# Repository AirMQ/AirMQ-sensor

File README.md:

# AirMQ-sensor
Root repository for AirMQ hardware project

AirMQ toolkit consists of main MCU and several sensor boards designed with common form factor in mind. Currently, particulate matter, radiation and electrochemical sensor boards are available. 

MCU board includes advanced power circuitry which makes possible the use of reduced consumption modes while powering from batteries or solar panels. All ESP8266’s gpio pins are accessible with a separate 16-pin connector sharing pin numbering with most popular development boards. 

All boards share the same type of extension connector which allows for stackability limited by sensors size.

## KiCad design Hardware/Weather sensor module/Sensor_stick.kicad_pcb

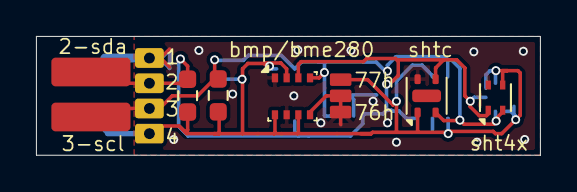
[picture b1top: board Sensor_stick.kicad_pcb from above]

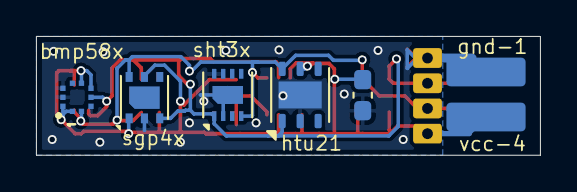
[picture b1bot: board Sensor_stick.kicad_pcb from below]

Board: 2 copper layers, 28.0 x 6.6 mm, 11 parts (5 on the bottom side), 4 nets.

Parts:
C1: 1 uF; C_0603_1608Metric_Pad1.08x0.95mm_HandSolder
J1: Conn_01x04; 4Pads
R1, R2: 4.7K; R_0603_1608Metric_Pad0.98x0.95mm_HandSolder
U1: SHT30-DIS; Sensirion_DFN-8-1EP_2.5x2.5mm_P0.5mm_EP1.1x1.7mm
U2: Si7021-A20; DFN-6-1EP_3x3mm_P1mm_EP1.5x2.4mm
U3: SHT4x; Sensirion_DFN-4_1.5x1.5mm_P0.8mm_SHT4x_NoCentralPad
U4: SHTC3; Sensirion_DFN-4-1EP_2x2mm_P1mm_EP0.7x1.6mm
U5: BME280; Bosch_LGA-8_2.5x2.5mm_P0.65mm_ClockwisePinNumbering
U6: SGP4x
U8: BMP580

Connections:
/SCL: J1.2, R2.2, U1.4 (SCL), U2.6 (SCL), U3.2 (SCL), U4.2 (SCL), U5.4 (SCK), U6.6 (SCL), U8.2 (SCK)
/SDA: J1.1, R1.2, U1.1 (SDA), U2.1 (SDA), U3.1 (SDA), U4.3 (SDA), U5.3 (SDI), U6.3 (SDA), U8.4 (SDI)
/VCC: C1.1, J1.3, R1.1, R2.1, U1.5 (VDD), U1.6 (~RESET), U2.5 (VDD), U3.3 (VDD), U4.1 (VDD), U5.2 (CSB), U5.6 (VDDIO), U5.8 (VDD), U6.1 (VDD), U6.5 (VDDH), U8.1 (VDDIO), U8.5 (SDO), U8.6 (CSB), U8.10 (VDD)
GND: C1.2, J1.4, U1.2 (ADDR), U1.7 (R), U1.8 (VSS), U1.9 (VSS), U2.2 (GND), U2.7 (PAD), U3.4 (VSS), U4.4 (VSS), U5.1 (GND), U5.7 (GND), U6.2 (VSS), U8.3 (VSS), U8.8 (VSS), U8.9 (VSS)

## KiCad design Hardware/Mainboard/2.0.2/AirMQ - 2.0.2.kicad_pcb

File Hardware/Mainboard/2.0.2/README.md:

# Mainboard version 2.0.2

Changelog:

3D view

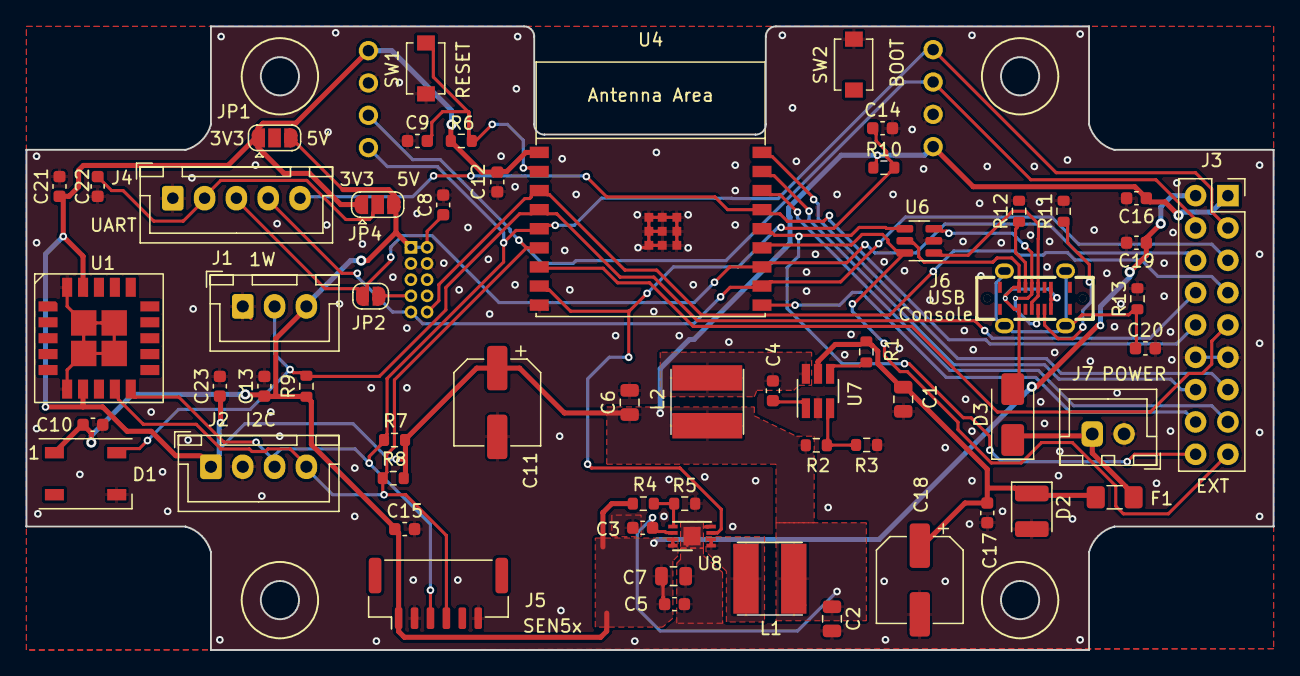
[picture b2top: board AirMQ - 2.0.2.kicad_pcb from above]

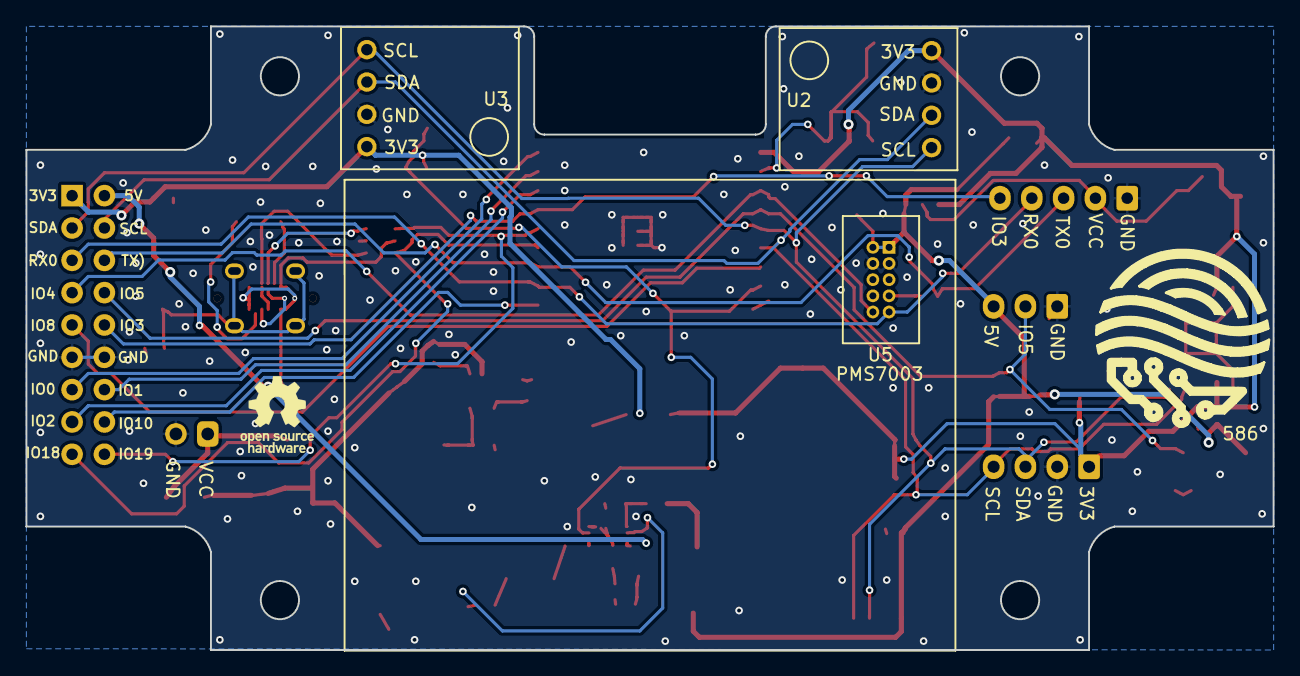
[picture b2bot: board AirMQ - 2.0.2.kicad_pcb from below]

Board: 2 copper layers, 98.0 x 49.0 mm, 63 parts (4 on the bottom side), 35 nets.

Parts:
586: AirMQ_Logo; AirMQ_Logo_new
C1, C2: 10 uF; C_0805_2012Metric
C3, C5, C10, C12, C13, C14, C15, C17, C20, C21, C22, C23: 0.1 uF; C_0603_1608Metric
C4: 22 nF; C_0603_1608Metric
C6, C7: 22 uF; C_0805_2012Metric
C8: 0.1; C_0603_1608Metric
C9, C16, C19: 1 uF; C_0603_1608Metric
C11: 330 uF; CP_Elec_6.3x7.7
C18: 100 uF; CP_Elec_6.3x7.7
D1: WS2812B; LED_WS2812B_PLCC4_5.0x5.0mm_P3.2mm
D2: D_TVS; D_1210_3225Metric
D3: SC34; D_SMA
F1: 0.5A; Fuse_1206_3216Metric_Pad1.42x1.75mm_HandSolder
J1: 1Wire/LED; JST_XH_B3B-XH-A_1x03_P2.50mm_Vertical
J2: I2C; JST_XH_B4B-XH-A_1x04_P2.50mm_Vertical
J3: EXT; PinSocket_2x09_P2.54mm_Vertical
J4: UART; JST_XH_B5B-XH-A_1x05_P2.50mm_Vertical
J5: SEN5x; JST_GH_BM06B-GHS-TBT_1x06-1MP_P1.25mm_Vertical
J6: USB_C; USB-C-SMD_TYPEC-303-ACP16
J7: MAIN_PWR; JST_XH_B2B-XH-A_1x02_P2.50mm_Vertical
JP1, JP4: SolderJumper_3_Open; SolderJumper-3_P1.3mm_Open_RoundedPad1.0x1.5mm
JP2: TX; SolderJumper-2_P1.3mm_Open_RoundedPad1.0x1.5mm
L1: 2.2 uH; Inductor_CD53
L2: 4.7 uH; Inductor_CD53
R1: 100k; R_0603_1608Metric
R2: 150k; R_0603_1608Metric
R3: 33k; R_0603_1608Metric
R4: 510k; R_0603_1608Metric
R5: 160k; R_0603_1608Metric
R6, R7, R8, R10: 10k; R_0603_1608Metric
R9: 4.7k; R_0603_1608Metric
R11, R12: 5.1k; R_0603_1608Metric
R13: 0R; R_0603_1608Metric
SW1: RESET; SW_PUSH_4x3x2
SW2: BOOT; SW_PUSH_4x3x2
U1: SCD40
U2, U3: GY-Sensor; GY-BMEP
U4: ESP32-C3-WROOM-02
U5: PMS7003
U6: USBLC6-2SC6; SOT-23-6
U7: STI3470; SOT-23-6_Handsoldering
U8: SY7088; DFN-8-1EP_3x2mm_P0.5mm_EP1.36x1.46mm

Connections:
+3V3: C2.1, C3.1, C6.1, C11.1, C12.1, C16.1, C21.1, C23.1, J2.1, J3.1, JP1.1 (A), JP4.1 (A), L1.1, L2.2, R2.1, R6.1, R7.1, R8.1, R10.1, U1.7 (VDD), U1.19 (VDDH), U2.1 (VCC), U3.1 (VCC), U4.1 (3V3), U8.6 (IN)
+5V: C5.1, C7.1, C8.1, C10.1, C13.1, C15.1, C19.1, D1.1 (VDD), J1.3, J3.2, J5.1, JP1.3 (B), JP4.3 (B), R4.1, R9.1, U5.1 (VCC), U5.2 (VCC), U8.7 (OUT), U8.8 (OUT)
/D+: J3.18, U4.14 (GPIO19/USB_D+), U6.4 (I/O2)
/D-: J3.17, U4.13 (GPIO18/USB_D-), U6.6 (I/O1)
/EN: C9.2, R6.2, SW1.2, U4.2 (EN/CHIP_PU)
/IO0: J3.13, U4.18 (GPIO0)
/IO1: J3.14, U4.17 (GPIO1)
/IO2: J3.15, U4.16 (GPIO2)
/IO3: J3.10, J4.5, U4.15 (GPIO3)
/IO4: J3.7, U4.3 (GPIO4), U5.10 (SET)
/IO5: D1.4 (DIN), J1.2, J3.8, R9.2, U4.4 (GPIO5)
/IO8: J3.9, U4.7 (GPIO8)
/IO9: C14.1, R10.2, U4.8 (GPIO9), U8.3 (EN)
/IO10: J3.16, U4.10 (GPIO10)
/RX0: J3.5, J4.4, U4.11 (GPIO20/U0RXD), U5.9 (TX)
/SCL: J2.4, J3.4, J5.4, R8.2, U1.9 (SCL), U2.3 (SCL), U3.3 (SCL), U4.6 (GPIO7)
/SDA: J2.3, J3.3, J5.3, R7.2, U1.10 (SDA), U2.4 (SDA), U3.4 (SDA), U4.5 (GPIO6)
/TX0: J3.6, J4.3, JP2.1 (A), U4.12 (GPIO21/U0TXD)
GND: C1.2, C2.2, C3.2, C5.2, C6.2, C7.2, C8.2, C9.1, C10.2, C11.2, C12.2, C13.2, C14.2, C15.2, C16.2, C17.2, C18.2, C19.2, C20.2, C21.2, C22.2, C23.2, D1.3 (VSS), D2.2 (A2), J1.1, J2.2, J3.11, J3.12, J4.1, J5.2, J5.6, J7.1, R3.2, R5.2, R11.2, R12.2, R13.2, SW1.1, SW2.2, U1.6 (GND), U1.20 (GND), U1.21 (GND), U2.2 (GND), U3.2 (GND), U4.9 (GND), U4.19 (GND), U5.3 (GND), U5.4 (GND), U6.2 (GND), U7.2 (GND), U8.4 (SGND), U8.9 (PGND)
unnamed: D3.2 (A), J6.A4 (VBUS), J6.A9 (VBUS), J6.B4 (VBUS), J6.B9 (VBUS), U6.5 (VBUS)
unnamed: D3.1 (K), F1.2, J7.2
unnamed: C22.1, J4.2, JP4.2 (C)
unnamed: J6.A5 (CC1), R11.1
unnamed: J6.B5 (CC2), R12.1
unnamed: J6.A6 (D+), J6.B6 (D+), U6.3 (I/O2)
unnamed: J6.A7 (D-), J6.B7 (D-), U6.1 (I/O1)
unnamed: C20.1, J6.S1 (SHIELD), R13.1
unnamed: JP2.2 (B), U5.7 (RX)
unnamed: L1.2, U8.1 (LX), U8.2 (LX)
unnamed: C4.1, U7.1 (BS)
unnamed: R1.2, U7.4 (EN)
unnamed: R2.2, R3.1, U7.3 (FB)
unnamed: C4.2, L2.1, U7.6 (LX)
unnamed: R4.2, R5.1, U8.5 (FB)
VCC: C1.1, C17.1, C18.1, D2.1 (A1), F1.1, R1.1, U7.5 (VIN)

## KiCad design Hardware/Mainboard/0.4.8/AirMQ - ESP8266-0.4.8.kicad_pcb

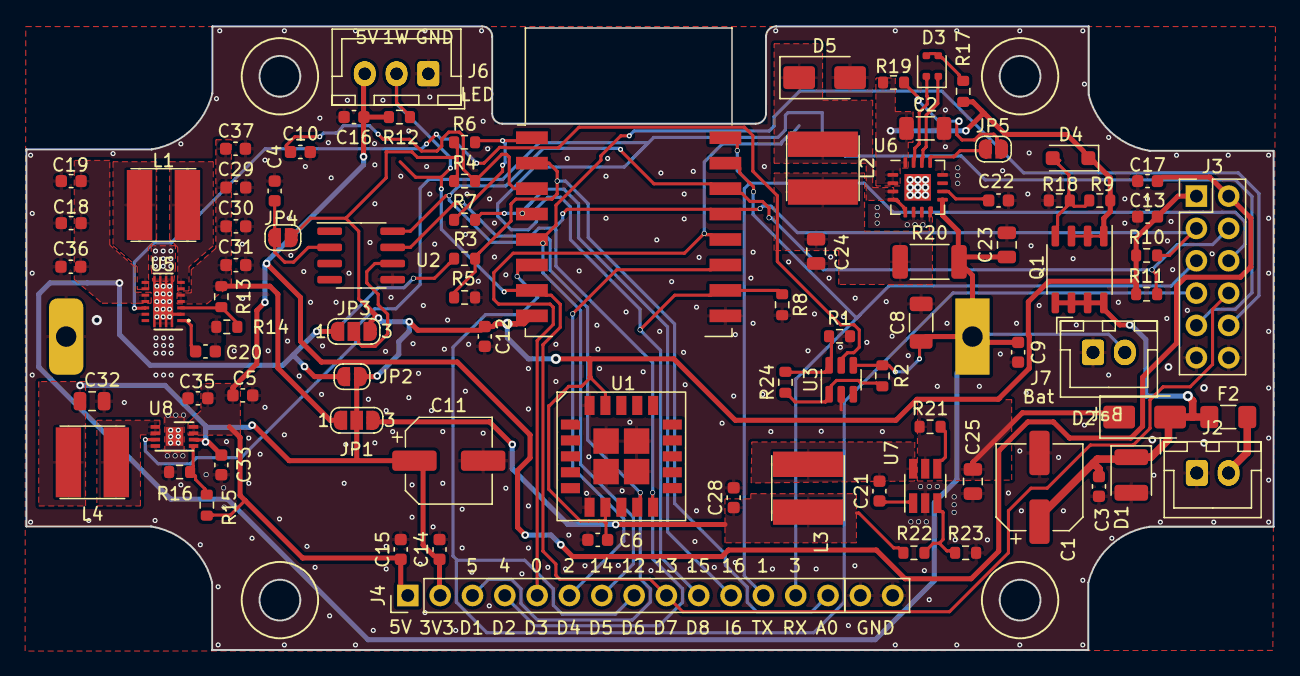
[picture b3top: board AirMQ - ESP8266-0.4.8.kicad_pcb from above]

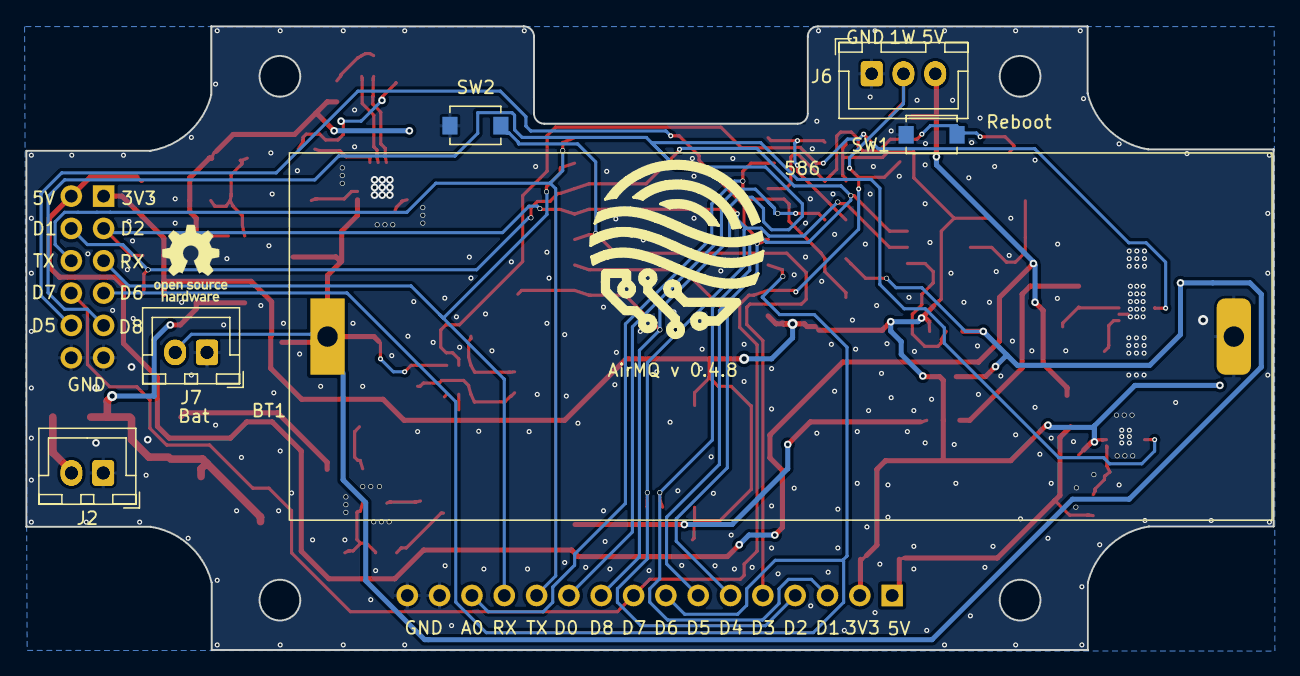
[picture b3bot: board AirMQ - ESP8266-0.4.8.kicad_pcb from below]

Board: 2 copper layers, 98.0 x 49.0 mm, 93 parts (7 on the bottom side), 48 nets.

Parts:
586: AirMQ_Logo; AirMQ_Logo_new
BT1: LiPo/ LiFePo4; 26650
C1: 100 uF; CP_Elec_6.3x7.7
C2: 22 uF; C_1206_3216Metric
C3, C4, C5, C6, C9, C10, C12, C14, C15, C16, C20, C22, C33, C36, C37: 100 nF; C_0603_1608Metric
C8: 100 uF; C_1206_3216Metric
C11: 330 uF; CP_Elec_6.3x7.7
C13: NP; C_0603_1608Metric
C17, C18, C19: 10 uF; C_0603_1608Metric
C21: 22 nF; C_0603_1608Metric
C23, C25, C32: 10 uF; C_0805_2012Metric
C24: 22 uF; C_0805_2012Metric
C28, C29, C30, C31, C35: 22 uF; C_0603_1608Metric
D1: D_TVS; D_1210_3225Metric
D2, D5: SC34; D_SMA
D3: LED_Dual_CCAA; LED_0603_Dual
D4: 5.1V; D_SOD-123F
F2: 0.5A; Fuse_1206_3216Metric_Pad1.42x1.75mm_HandSolder
J2, J2#2: MAIN_PWR; JST_XH_B2B-XH-A_1x02_P2.50mm_Vertical
J3: ExpBoard; PinHeader_2x06_P2.54mm_Vertical_CC
J4: Dev; PinHeader_1x16_P2.54mm_Vertical
J6, J6#2: 1Wire/LED; JST_XH_B3B-XH-A_1x03_P2.50mm_Vertical
J7, J7#2: Bat; JST_XH_B2B-XH-A_1x02_P2.50mm_Vertical
JP1: 3.3V Source; SolderJumper-3_P1.3mm_Open_RoundedPad1.0x1.5mm_NumberLabels
JP2: LiFe/LiPo; SolderJumper-2_P1.3mm_Open_RoundedPad1.0x1.5mm
JP3: RTC Source; SolderJumper-3_P1.3mm_Open_RoundedPad1.0x1.5mm_NumberLabels
JP4: VCC Bypass; SolderJumper-2_P1.3mm_Open_RoundedPad1.0x1.5mm
JP5: LiPo/LiFe; SolderJumper-2_P1.3mm_Open_RoundedPad1.0x1.5mm
L1: 1.5 uH; Inductor_CD53
L2, L3: 4.7 uH; Inductor_CD53
L4: 2.2 uH; Inductor_CD53
Q1: TPC8107; SOP-8_3.9x4.9mm_P1.27mm
R1: 270k; R_0603_1608Metric
R2: 390k; R_0603_1608Metric
R3: 330k; R_0603_1608Metric
R4, R6, R8, R19: 10k; R_0603_1608Metric
R5, R21: 100k; R_0603_1608Metric
R7: 100; R_0603_1608Metric
R9: 316k; R_0603_1608Metric
R10, R11, R12: 4.7k; R_0603_1608Metric
R13: 1M; R_0603_1608Metric
R14: 180k; R_0603_1608Metric
R15: 510k; R_0603_1608Metric
R16: 160k; R_0603_1608Metric
R17: 1k; R_0603_1608Metric
R18: 20k; R_0603_1608Metric
R20: 0.2; R_2010_5025Metric
R22: 150k; R_0603_1608Metric
R23: 33k; R_0603_1608Metric
R24: 39k; R_0603_1608Metric
SW1: RESET; SW_PUSH_4x3x2
SW2: HW_RESET; SW_PUSH_4x3x2
U1: SCD40
U2: DS3231MZ; SOIC-8_3.9x4.9mm_P1.27mm
U3: CN302; SOT-23-6
U4: ESP-07; ESP-12E_noSPI
U5: TPS63020; QFN14-3X4MM
U6: TP5000; QFN-16-1EP_4x4mm_P0.65mm_EP2.1x2.1mm
U7: STI3470; SOT-23-6_Handsoldering
U8: SY7088; DFN-8-1EP_3x2mm_P0.5mm_EP1.36x1.46mm

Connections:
+3V3: C6.1, C11.1, C12.1, C13.1, C14.1, C32.1, C33.1, J3.1, J4.2, JP1.2 (C), JP2.2 (B), JP3.3 (B), JP4.2 (B), L4.1, R4.1, R6.1, R10.1, R11.1, U1.7 (VDD), U1.19 (VDDH), U4.8 (VCC), U8.6 (IN)
+5V: C5.1, C15.1, C16.1, C17.1, C35.1, J3.12, J4.1, J6.3, J6#2.3, R12.1, R15.1, U8.7 (OUT), U8.8 (OUT)
+BATT: BT1.1 (+), C8.1, C9.1, C18.1, C19.1, C23.1, C36.1, J7.2, J7#2.2, JP2.1 (A), JP3.1 (A), R2.1, R3.2, R20.2, U3.4 (VCC), U5.10 (VIN), U5.11 (VIN), U6.9 (BAT)
/A0: J4.14, R3.1, R5.1, U4.2 (ADC)
/BoostEn: J3.5, J4.10, R8.1, U4.10 (GPIO15), U8.3 (EN)
/D0: J4.11, R7.2, U4.4 (GPIO16)
/D1: J3.11, J4.3, R11.2, U1.9 (SCL), U2.8 (SCL), U4.14 (GPIO5)
/D2: J3.2, J4.4, R10.2, U1.10 (SDA), U2.7 (SDA), U4.13 (GPIO4)
/D3: J4.5, SW2.2, U4.12 (GPIO0)
/D4: J4.6, U4.11 (GPIO2)
/D5: J3.8, J4.7, U4.5 (GPIO14)
/D6: J3.4, J4.8, U4.6 (GPIO12)
/D7: J3.9, J4.9, J6.2, J6#2.2, R12.2, U4.7 (GPIO13)
/P_Good: U3.5 (LBI), U5.12 (EN)
/RX0: J3.3, J4.13, U4.15 (GPIO3/RXD)
/TX0: J3.10, J4.12, U4.16 (GPIO1/TXD)
GND: BT1.2 (-), C1.2, C2.2, C3.2, C4.2, C5.2, C6.2, C8.2, C9.2, C10.2, C11.2, C12.2, C13.2, C14.2, C15.2, C16.2, C17.2, C18.2, C19.2, C20.2, C22.2, C23.2, C24.2, C25.2, C28.2, C29.2, C30.2, C31.2, C32.2, C33.2, C35.2, C36.2, C37.2, D1.2 (A2), D5.2 (A), J2.1, J2#2.1, J3.6, J3.7, J4.15, J4.16, J6.1, J6#2.1, J7.1, J7#2.1, R1.2, R5.2, R8.2, R14.2, R16.2, R18.2, R23.2, SW1.1, SW2.1, U1.6 (GND), U1.20 (GND), U1.21 (GND), U2.5 (GND), U3.2 (GND), U4.9 (GND), U5.2 (GND), U5.13 (PS/SYN), U5.15 (PGND), U5.16 (PGND), U5.17 (PGND), U5.18 (PGND), U5.19 (PGND), U5.20 (PGND), U5.21 (PGND), U5.22 (PGND), U5.23 (PGND), U6.6 (GND), U6.7 (GND), U6.12 (RTRK), U6.17 (GND), U7.2 (GND), U8.4 (SGND), U8.9 (PGND)
unnamed: C25.1, D2.1 (K), R21.1, U7.5 (VIN)
unnamed: D3.3 (A1), D3.4 (A2), R17.2
unnamed: D3.2 (K1), U6.15 (CHRG)
unnamed: D3.1 (K2), U6.14 (STBY)
unnamed: D4.2 (A), Q1.4 (G), R9.2, R18.1
unnamed: C2.1, D4.1 (K), Q1.1 (S), Q1.2 (S), Q1.3 (S), R9.1, R17.1, R19.2, U6.1 (Vin), U6.2 (Vin), U6.16 (Vin)
unnamed: D5.1 (K), L2.1, U6.3 (LX), U6.4 (LX), U6.5 (LX)
unnamed: F2.2, J2.2, J2#2.2
unnamed: C29.1, C30.1, C31.1, C37.1, JP1.1 (A), R13.1, U5.4 (VOUT), U5.5 (VOUT)
unnamed: C28.1, JP1.3 (B), L3.2, R22.1
unnamed: JP3.2 (C), U2.6 (VBAT)
unnamed: C4.1, JP4.1 (A), U2.2 (VCC)
unnamed: JP5.1 (A), R19.1
unnamed: JP5.2 (B), U6.13 (CS)
unnamed: L1.1, U5.8 (L1), U5.9 (L1)
unnamed: L1.2, U5.6 (L2), U5.7 (L2)
unnamed: L4.2, U8.1 (LX), U8.2 (LX)
unnamed: R2.2, R24.1, U3.1 (FTH)
unnamed: R1.1, R24.2, U3.6 (RTH)
unnamed: C10.1, R4.2, SW1.2, U4.3 (EN)
unnamed: R6.2, R7.1, U4.1 (~RST)
unnamed: R13.2, R14.1, U5.3 (FB)
unnamed: C20.1, U5.1 (VINA)
unnamed: C22.1, U6.10 (VREG)
unnamed: C24.1, L2.2, R20.1, U6.8 (VS)
unnamed: C21.1, U7.1 (BS)
unnamed: R21.2, U7.4 (EN)
unnamed: R22.2, R23.1, U7.3 (FB)
unnamed: C21.2, L3.1, U7.6 (LX)
unnamed: R15.2, R16.1, U8.5 (FB)
VCC: C1.1, C3.1, D1.1 (A1), D2.2 (A), F2.1, Q1.5 (D), Q1.6 (D), Q1.7 (D), Q1.8 (D)

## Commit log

2020-05-21 Create readme.md . ...
2020-05-21 Create . ...
2020-05-21 Create . ..
2020-05-23 Create Schematic
2020-05-23 Create . ...
2020-05-28 added boards description
2020-05-28 added some formatting
2020-07-31 Add files via upload
    Main case part
2020-07-31 Graphics
2022-07-22 minor corrections
2022-11-02 2-way air duct for PMS7003
2023-03-16 Create 20230309
2023-03-16 Add files via upload
    Filesystem image
2023-03-16 Filesystem image file
2023-03-16 OTA upgrade file
2023-09-11 added v0.4.9
2023-09-11 added v0.4.1
2023-09-11 cleanup
2024-02-10 added .sch file
2024-02-10 added .pcb file
2024-02-10 added 0.4.8 pcb
2024-02-10 added pdf schematics
2024-02-11 added v2 housing
2024-10-07 add 20241007_AirMQ_ESP32s3_16M8M_LittleFS_CDC.bin
2024-10-07 version 20241007 for ESP32-S3, OTA upgrade
2024-10-07 version 20241007 for ESP32-S3, for initial upload
2026-01-27 Added mainboard v2.0.2
2026-01-27 Added README.md and stl file
2026-01-27 moved files to v1
2026-01-27 added schematic pdf
2026-01-27 added weather sensor module
2026-01-27 added STEP file
